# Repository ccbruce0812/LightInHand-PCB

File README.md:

# LightInHand-PCB
PCB of [LightInHand](https://github.com/ccbruce0812/LightInHand.git)

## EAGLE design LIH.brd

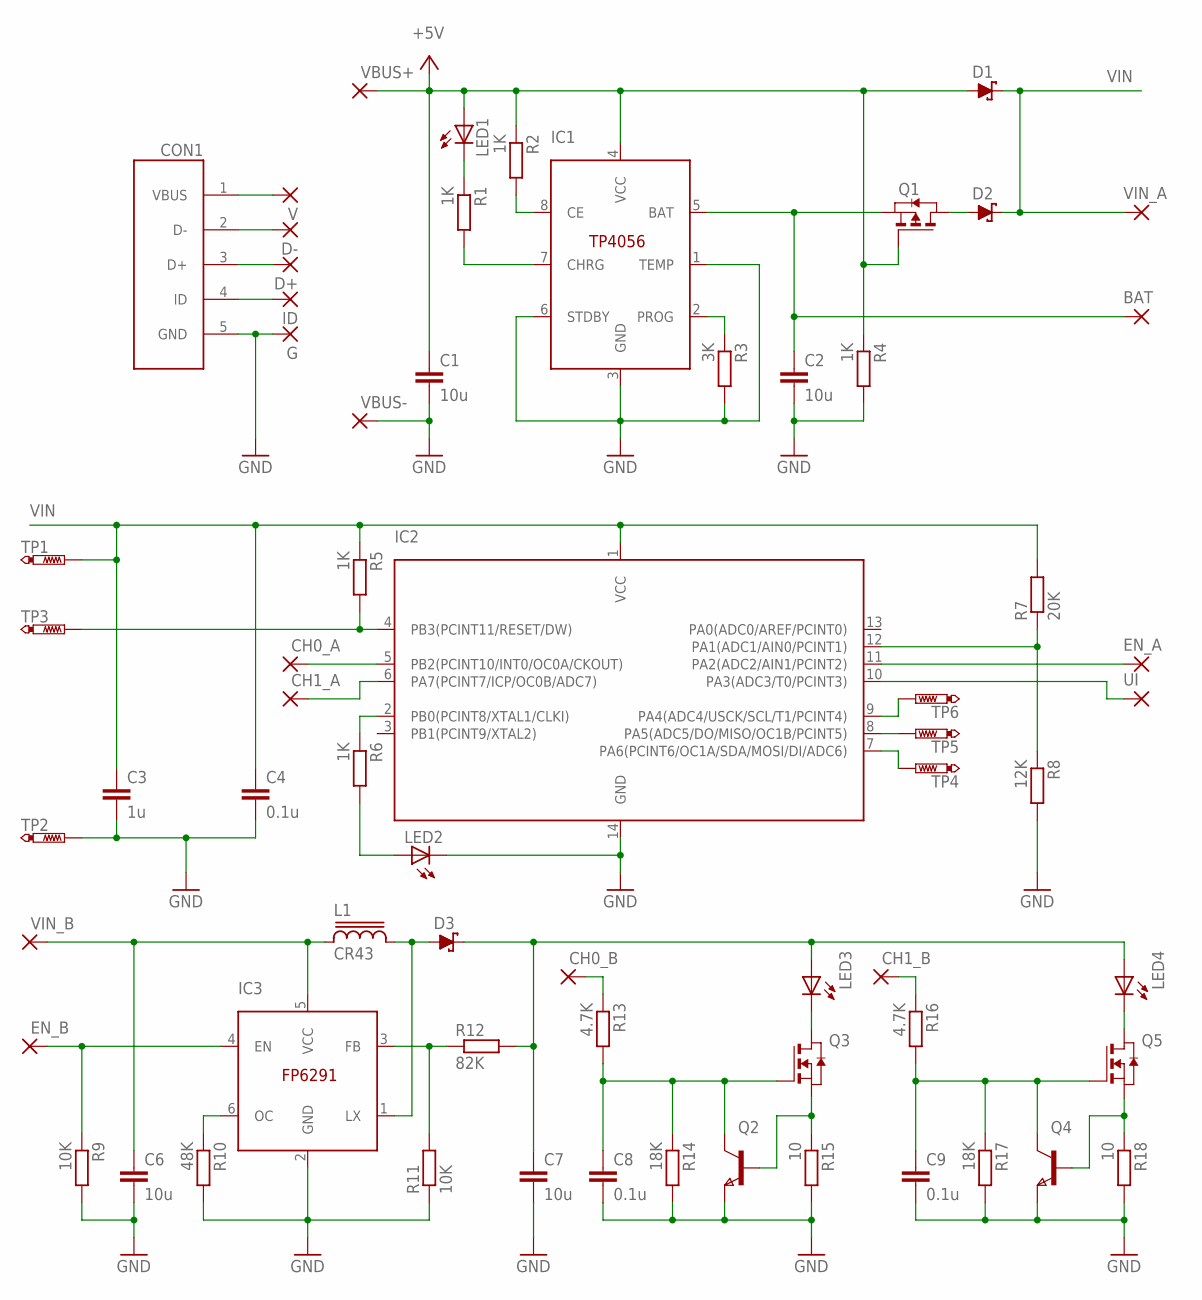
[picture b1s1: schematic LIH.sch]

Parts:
BAT: WIREPADSMD1,27-254; 1,6/0,8
C1, C2, C6, C7: 10u; C0805K
C3: 1u; C0805K
C4, C8, C9: 0.1u; C0805K
CH0_A, CH0_B, CH1_A, CH1_B: 1,6/0,8
CON1: MK5P
D1, D2, D3: SCHOTTKYSCHOTTKY-DO214AC; DO214AC
D+: SMD2; SMD1,27-2,54
D-: SMD2; SMD1,27-2,54
EN_A: WIREPADSMD1,27-254; 1,6/0,8
EN_B: WIREPADSMD1,27-254; 1,6/0,8
G: SMD2; SMD1,27-2,54
IC1: TP4056; SO8
IC2: ATTINY24A; SO14
IC3: FP6291; SOT-23-6
ID: SMD2; SMD1,27-2,54
L1: CR43
LED1, LED2: LEDSML0805; SML0805
LED3, LED4: 2835
Q1: PMOSSOT23; SOT-23
Q2, Q4: NPNSOT23; SOT-23
Q3, Q5: NMOSSOT23; SOT-23
R1, R2, R4, R5, R6: 1K; R0805
R3: 3K; R0805
R7: 20K; R0805
R8: 12K; R0805
R9, R11: 10K; R0805
R10: 48K; R0805
R12: 82K; R0805
R13, R16: 4.7K; R0805
R14, R17: 18K; R0805
R15, R18: 10; R0805
TP1, TP2, TP3, TP4, TP5, TP6: PTR1TP10R; TP10R
UI: WIREPADSMD1,27-254; 1,6/0,8
V: SMD2; SMD1,27-2,54
VBUS+: WIREPADSMD1,27-254; 1,6/0,8
VBUS-: WIREPADSMD1,27-254; 1,6/0,8
VIN_A: WIREPADSMD1,27-254; 1,6/0,8
VIN_B: WIREPADSMD1,27-254; 1,6/0,8

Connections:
5V6: C7.1, D3.C, LED3.1 (A), LED4.1 (A), R12.2
+5V: C1.1, D1.A, IC1.4 (VCC), LED1.A, Q1.3 (G), R2.1, R4.1, VBUS+.1
BAT: BAT.1, C2.1, IC1.5 (BAT), Q1.2 (S)
GND: C1.2, C2.2, C3.2, C4.2, C6.2, C7.2, C8.2, C9.2, CON1.5 (GND), G.1, IC1.1 (TEMP), IC1.3 (GND), IC1.6 (STDBY), IC2.14 (GND), IC3.2 (GND), LED2.C, Q2.2 (E), Q4.2 (E), R3.2, R4.2, R8.2, R9.2, R10.2, R11.1, R14.2, R15.2, R17.2, R18.2, TP2.TP, VBUS-.1
unnamed: CON1.1 (VBUS), V.1
unnamed: LED2.A, R6.2
unnamed: D2.A, Q1.1 (D)
unnamed: IC2.7 (PA6(PCINT6/OC1A/SDA/MOSI/DI/ADC6)), TP4.TP
unnamed: IC1.7 (CHRG), R1.2
unnamed: IC1.8 (CE), R2.2
unnamed: Q4.3 (B), Q5.2 (S), R18.1
unnamed: LED1.C, R1.1
unnamed: IC1.2 (PROG), R3.1
unnamed: IC3.6 (OC), R10.1
unnamed: IC2.8 (PA5(ADC5/DO/MISO/OC1B/PCINT5)), TP5.TP
unnamed: D3.A, IC3.1 (LX), L1.2
unnamed: LED3.2 (C), Q3.1 (D)
unnamed: LED4.2 (C), Q5.1 (D)
unnamed: IC3.3 (FB), R11.2, R12.1
unnamed: C8.1, Q2.1 (C), Q3.3 (G), R13.2, R14.1
unnamed: Q2.3 (B), Q3.2 (S), R15.1
unnamed: C9.1, Q4.1 (C), Q5.3 (G), R16.2, R17.1
unnamed: CON1.2 (D-), D-.1
unnamed: CON1.3 (D+), D+.1
unnamed: CON1.4 (ID), ID.1
unnamed: IC2.9 (PA4(ADC4/USCK/SCL/T1/PCINT4)), TP6.TP
unnamed: IC2.4 (PB3(PCINT11/RESET/DW)), R5.2, TP3.TP
unnamed: CH0_A.1, IC2.5 (PB2(PCINT10/INT0/OC0A/CKOUT))
unnamed: CH1_A.1, IC2.6 (PA7(PCINT7/ICP/OC0B/ADC7))
unnamed: CH0_B.1, R13.1
unnamed: EN_A.1, IC2.11 (PA2(ADC2/AIN1/PCINT2))
unnamed: IC2.12 (PA1(ADC1/AIN0/PCINT1)), R7.1, R8.1
unnamed: CH1_B.1, R16.1
unnamed: IC2.10 (PA3(ADC3/T0/PCINT3)), UI.1
unnamed: EN_B.1, IC3.4 (EN), R9.1
unnamed: IC2.2 (PB0(PCINT8/XTAL1/CLKI)), R6.1
unnamed: C6.1, IC3.5 (VCC), L1.1, VIN_B.1
VIN: C3.1, C4.1, D1.C, D2.C, IC2.1 (VCC), R5.1, R7.2, TP1.TP, VIN_A.1

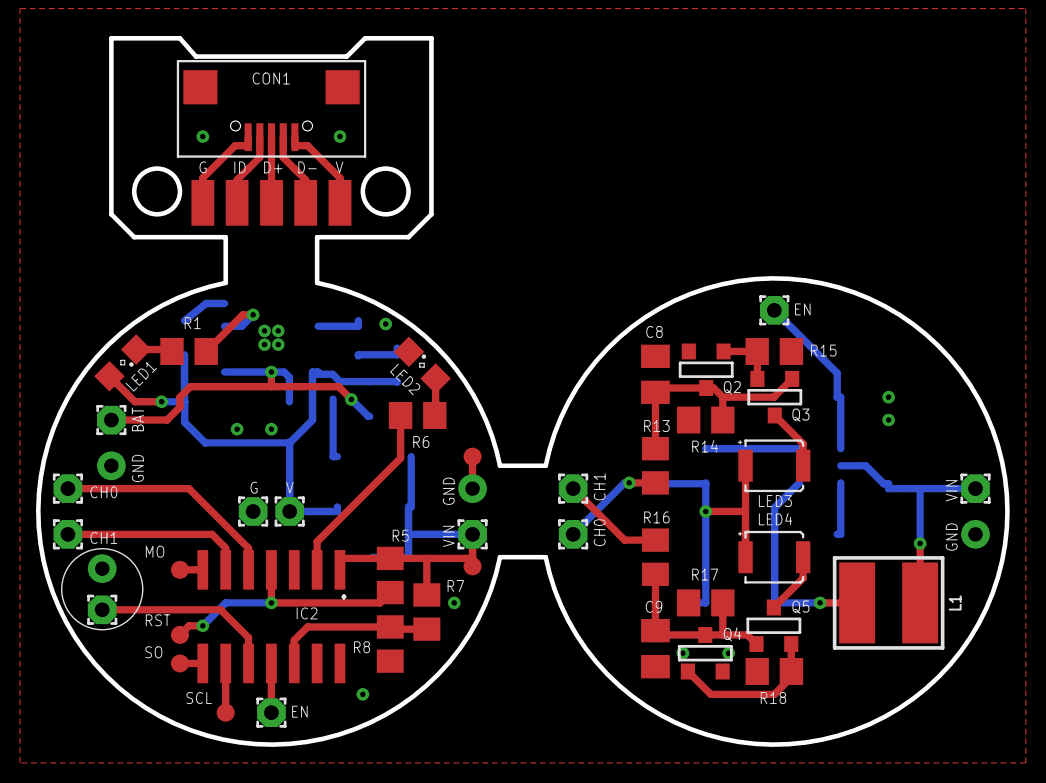
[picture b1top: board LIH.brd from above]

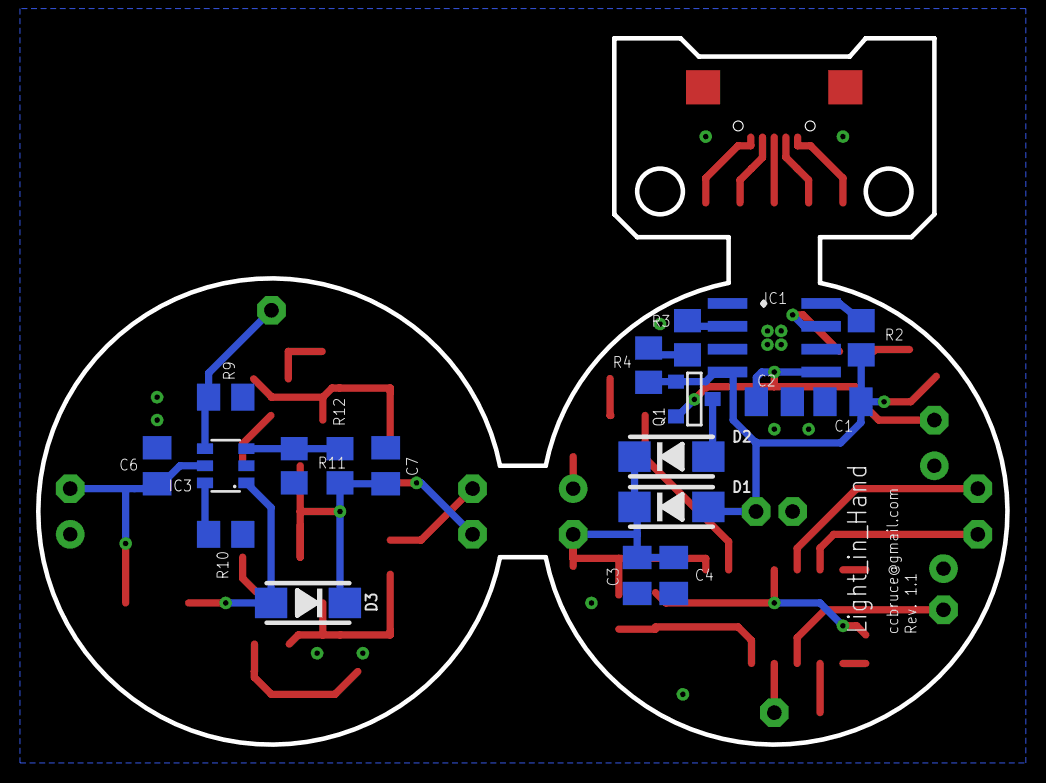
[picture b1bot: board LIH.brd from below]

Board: 2 copper layers, 53.8 x 39.2 mm, 66 parts (19 on the bottom side), 38 nets.

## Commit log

2018-06-24 Draft version.
2018-06-24 Amend README. Amend README. Amend README. Amend README. Amend README. Amend README. Amend README. Amend README. Amend README. Amend README. Amend README.
